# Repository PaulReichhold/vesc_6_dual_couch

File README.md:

# Compact High Power Motor Controller
Based on the VESC-Project of Benjamin Vedder

## Specs
| Spec | Tested to |
|---------|-------|
|__Voltage:__| 6.5V - 50.4V |
|__max Phase Current:__| 180A |
|__max Power (dual, with active cooling)__| 15kW |

> [!NOTE]
> One side has the current measurment inverted (forgot which one it was)

> [!WARNING]
> Use the provided design at your own risk

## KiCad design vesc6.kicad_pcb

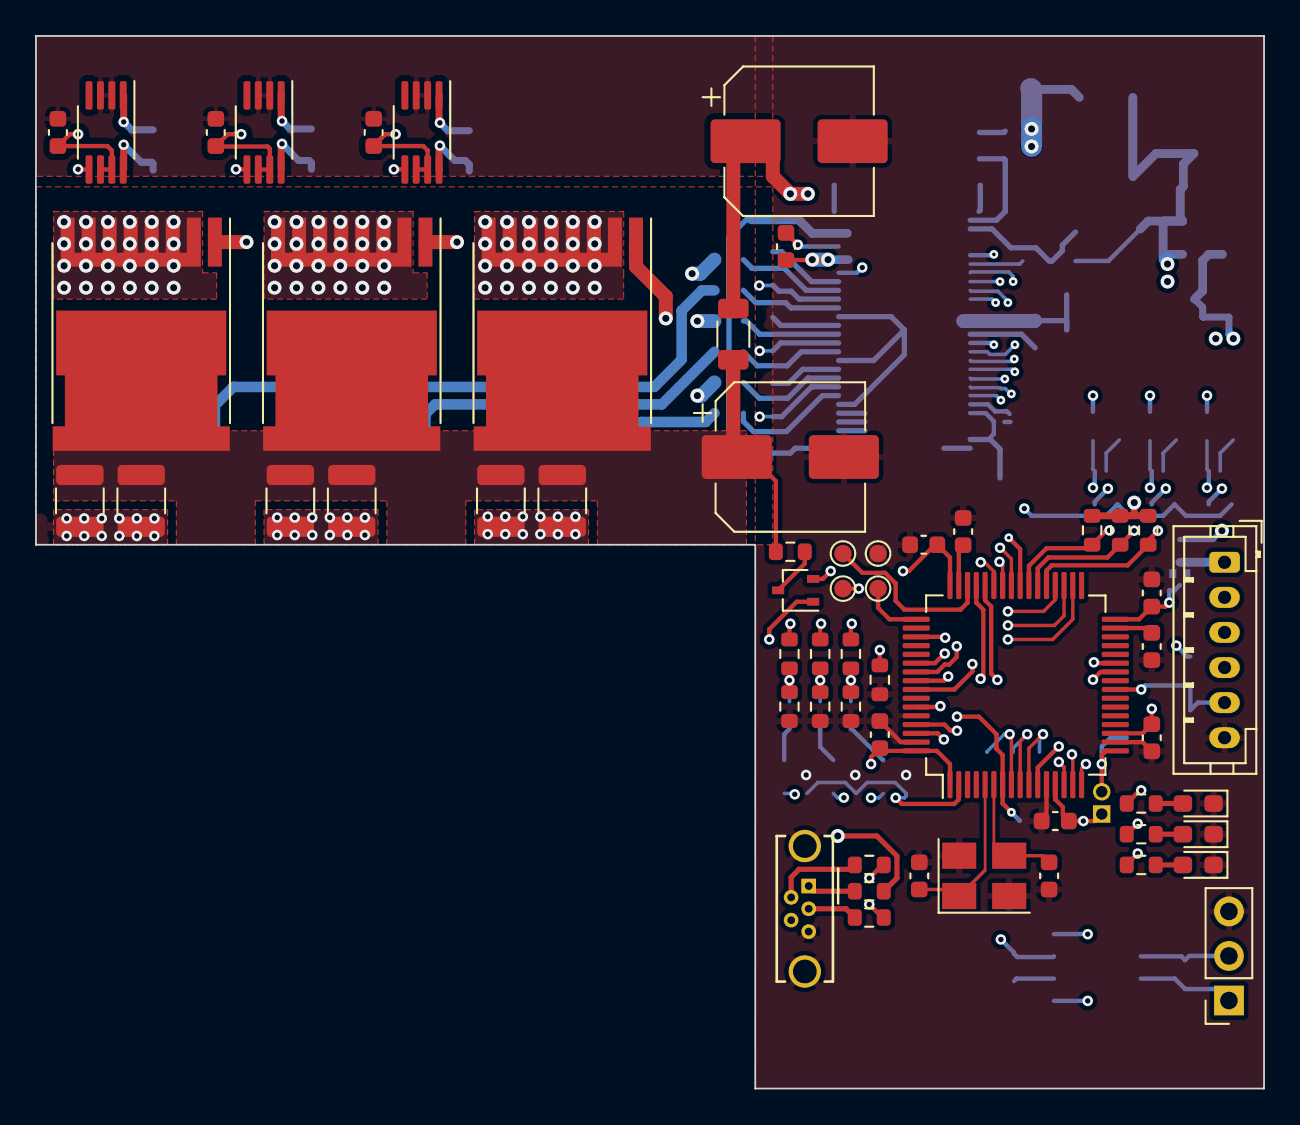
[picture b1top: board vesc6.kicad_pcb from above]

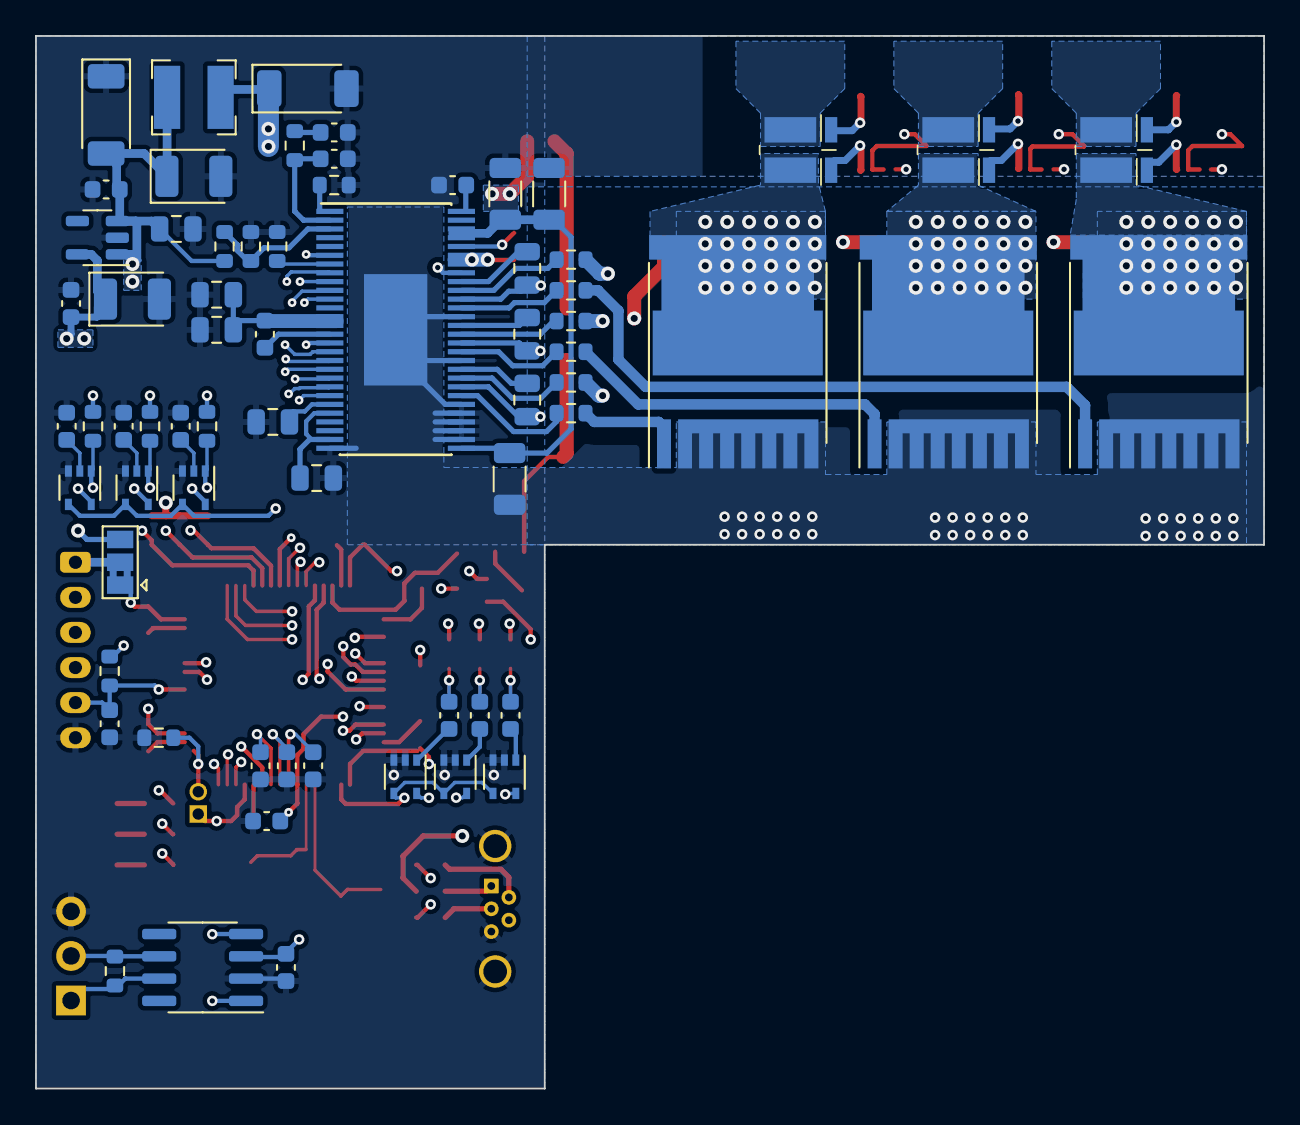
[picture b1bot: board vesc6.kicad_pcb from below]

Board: 4 copper layers, 70.0 x 60.0 mm, 126 parts (67 on the bottom side), 98 nets.

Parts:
C3, C5, C6, C7, C8, C9, C12, C20, C23, C26, C27, C57: 100n; C_0603_1608Metric
C10, C11: 15p; C_0603_1608Metric
C13, C14: 1u; C_0603_1608Metric
C15: 6n8; C_0603_1608Metric
C16, C17, C18, C21, C33: 2.2u; C_0805_2012Metric
C19: 120p; C_0603_1608Metric
C22: 22n; C_0603_1608Metric
C24, C39, C46, C52: 15n; C_0603_1608Metric
C25, C31, C32: 4.7u; C_1206_3216Metric
C28, C29, C30: 220n; C_0805_2012Metric
C34, C37: 100u; CP_EIA-3528-21_Kemet-B
C35, C36, C38, C44, C51: 2.2u; C_0603_1608Metric
C40, C48, C53: 1n; C_0603_1608Metric
C41, C42, C49, C50, C54, C55: 4.7u; C_1210_3225Metric
C56, C58: 22u; CP_Elec_8x6.2
D5: GRN; LED_0603_1608Metric_Pad1.05x0.95mm_HandSolder
D6: RED; LED_0603_1608Metric_Pad1.05x0.95mm_HandSolder
D7: BLU; LED_0603_1608Metric_Pad1.05x0.95mm_HandSolder
D8: D_Schottky; D_SOD-128
D9: 5V; D_SOD-128
FB1: FerriteBead; R_1206_3216Metric
J1: Main; PinSocket_1x03_P2.54mm_Vertical
J2: HALL_ENC; JST_PH_B6B-PH-K_1x06_P2.00mm_Vertical
J6: USB; USB_Micro-B_Wuerth_614105150721_Vertical_CircularHoles
L1: 22u; L_Bourns-SRN4018
Q1: DMN62D0UW; SOT-323_SC-70
Q2, Q3, Q4, Q5, Q6, Q7: HYG015N10NS1TA; Infineon_PG-HSOF-8-1
R6, R7, R8, R21, R25, R27, R29: 2.2k; R_0603_1608Metric
R10: 0; R_0603_1608Metric
R11, R23, R30: 10k; R_0603_1608Metric
R12, R13: 22; R_0603_1608Metric
R14, R15: 220; R_0603_1608Metric
R16, R34, R38, R40: 1k; R_0603_1608Metric
R17: 3.3k; R_0603_1608Metric
R18: 18k; R_0603_1608Metric
R19: 15k; R_0603_1608Metric
R20, R24, R26: 39k; R_0603_1608Metric
R22: 220k; R_0603_1608Metric
R28: 39K; R_0603_1608Metric
R31, R35, R39: 0.5m; BVN_1216
R32, R33, R36, R37, R41, R42: 4.7; R_0603_1608Metric
R43: 120; R_0603_1608Metric
SW1: SENS_VOLTAGE; SolderJumper-3_P1.3mm_Bridged2Bar12_Pad1.0x1.5mm
TH1: NTC; PinHeader_1x02_P1.27mm_Vertical
TP1: SWCLK; TestPoint_Pad_D1.0mm
TP2: SWDIO; TestPoint_Pad_D1.0mm
TP3: NRST; TestPoint_Pad_D1.0mm
TP4: GND; TestPoint_Pad_D1.0mm
U1: STM32F405RGTx; LQFP-64_10x10mm_P0.5mm
U2, U4, U5, U8, U9, U11: Mc74VHC1GT66; SOT-353_SC-70-5
U3: DRV8301DCAR; HTSSOP-56-1EP_6.1x14mm_P0.5mm_EP3.61x6.35mm
U6: TLV73333PDBV; SOT-23-5
U7, U10, U12: AD8418; MSOP-8_3x3mm_P0.65mm
U14: SN65HVD232; SOIC-8_3.9x4.9mm_P1.27mm
Y1: 8M; Crystal_SMD_EuroQuartz_MT-4Pin_3.2x2.5mm_HandSoldering

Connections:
/VESC_Right/3.3V: C5.1, C6.1, C7.1, C8.1, C9.1, C36.1, C37.1, C38.2, C44.2, C51.2, C57.1, R11.2, R16.2, SW1.1 (A), TH1.1, U1.1 (VBAT), U1.13 (VDDA), U1.19 (VDD), U1.32 (VDD), U1.48 (VDD), U1.64 (VDD), U2.5 (VCC), U3.49 (VDD_SPI), U4.5 (VCC), U5.5 (VCC), U6.5 (OUT), U7.6 (VS), U7.7 (REF1), U8.5 (VCC), U9.5 (VCC), U10.6 (VS), U10.7 (REF1), U11.5 (VCC), U12.6 (VS), U12.7 (REF1), U14.3 (VCC)
/VESC_Right/5V: C33.1, C34.1, C35.1, D9.2 (A2), L1.2, Q1.1 (G), R10.2, R18.2, SW1.3 (C), U6.1 (IN), U6.3 (EN)
/VESC_Right/CAN/RX: U1.61 (PB8), U14.4 (R)
/VESC_Right/CAN/TX: U1.62 (PB9), U14.1 (D)
/VESC_Right/CAN_H: J1.1, R43.1, U14.7 (CANH)
/VESC_Right/CAN_L: J1.2, R43.2, U14.6 (CANL)
/VESC_Right/DRV8301/CS: U1.40 (PC9), U3.8 (*SCS)
/VESC_Right/DRV8301/EN_GATE: U1.57 (PB5), U3.16 (EN_GATE)
/VESC_Right/DRV8301/FAULT: U1.59 (PB7), U3.6 (*FAULT)
/VESC_Right/DRV8301/GH_A: R32.1, U3.47 (GH_A)
/VESC_Right/DRV8301/GH_B: R36.1, U3.42 (GH_B)
/VESC_Right/DRV8301/GH_C: R41.1, U3.37 (GH_C)
/VESC_Right/DRV8301/GL_A: R33.1, U3.45 (GL_A)
/VESC_Right/DRV8301/GL_B: R37.1, U3.40 (GL_B)
/VESC_Right/DRV8301/GL_C: R42.1, U3.35 (GL_C)
/VESC_Right/DRV8301/INH_A: U1.41 (PA8), U3.17 (INH_A)
/VESC_Right/DRV8301/INH_B: U1.42 (PA9), U3.19 (INH_B)
/VESC_Right/DRV8301/INH_C: U1.43 (PA10), U3.21 (INH_C)
/VESC_Right/DRV8301/INL_A: U1.34 (PB13), U3.18 (INL_A)
/VESC_Right/DRV8301/INL_B: U1.35 (PB14), U3.20 (INL_B)
/VESC_Right/DRV8301/INL_C: U1.36 (PB15), U3.22 (INL_C)
/VESC_Right/DRV8301/SCLK: U1.51 (PC10), U3.11 (SCLK)
/VESC_Right/DRV8301/SDI: U1.56 (PB4), U3.9 (SDI)
/VESC_Right/DRV8301/SDO: U1.55 (PB3), U3.10 (SDO)
/VESC_Right/DRV8301/SENS_A: C20.1, R20.2, R21.2, U1.14 (PA0)
/VESC_Right/DRV8301/SENS_B: C23.1, R24.2, R25.2, U1.15 (PA1)
/VESC_Right/DRV8301/SENS_C: C26.1, R26.2, R27.2, U1.16 (PA2)
/VESC_Right/DRV8301/SENS_FILTERED: U1.2 (PC13), U2.4 (ON_OFF), U4.4 (ON_OFF), U5.4 (ON_OFF)
/VESC_Right/DRV8301/SENS_SUPPLY: Q1.2 (S), R29.1, U1.11 (PC3)
/VESC_Right/DRV8301/SH_B: C29.1, Q4.2 (S), Q5.3 (D), R24.1, R35.1, U3.41 (SH_B)
/VESC_Right/DRV8301/SH_C: C30.1, Q4.1 (G), Q6.2 (S), Q7.3 (D), R26.1, R36.2, R39.1, U3.36 (SH_C)
/VESC_Right/DRV8301/SUPPLY: C41.1, C42.1, C49.1, C50.1, C54.1, C55.1, C56.1, FB1.2, Q2.3 (D), Q4.3 (D), Q6.3 (D), R28.1
/VESC_Right/DRV8301/Supply_Filterted: C25.1, C31.1, C32.1, C58.1, FB1.1, U3.29 (PVDD1), U3.53 (PVDD2), U3.54 (PVDD2)
/VESC_Right/MCU/ADC_TEMP: R30.2, TH1.2, U1.17 (PA3)
/VESC_Right/MCU/CURRENT_1: C40.2, R34.1, U1.8 (PC0), U8.1 (IO_XA)
/VESC_Right/MCU/CURRENT_2: C48.2, R38.1, U1.9 (PC1), U9.1 (IO_XA)
/VESC_Right/MCU/CURRENT_3: C53.2, R40.1, U1.10 (PC2), U11.1 (IO_XA)
/VESC_Right/MCU/CURR_FILTER_ON: U1.54 (PD2), U8.4 (ON_OFF), U9.4 (ON_OFF), U11.4 (ON_OFF)
/VESC_Right/MCU/HALL_1: J2.2, R6.2, U1.37 (PC6)
/VESC_Right/MCU/HALL_2: J2.3, R7.2, U1.38 (PC7)
/VESC_Right/MCU/HALL_3: J2.4, R8.2, U1.39 (PC8)
/VESC_Right/MCU/LED_GREEN: R14.2, U1.26 (PB0)
/VESC_Right/MCU/LED_RED: R15.2, U1.27 (PB1)
/VESC_Right/MCU/NRST: C12.1, TP3.1, U1.7 (NRST)
/VESC_Right/MCU/SWCLK: TP1.1, U1.49 (PA14)
/VESC_Right/MCU/SWDIO: TP2.1, U1.46 (PA13)
/VESC_Right/MCU/TEMP_MOTOR: C3.1, J2.5, R11.1, U1.24 (PC4)
/VESC_Right/MCU/USB_D_N: R13.2, U1.44 (PA11)
/VESC_Right/MCU/USB_D_P: R12.2, U1.45 (PA12)
/VESC_Right/Power/C_A: R34.2, U7.5 (OUT)
/VESC_Right/Power/C_B: R38.2, U10.5 (OUT)
/VESC_Right/Power/C_C: R40.2, U12.5 (OUT)
/VESC_Right/SH_A: C28.1, Q2.2 (S), Q3.3 (D), R20.1, R31.1, U3.46 (SH_A)
GND: C3.2, C5.2, C6.2, C7.2, C8.2, C9.2, C10.2, C11.2, C12.2, C13.2, C14.2, C15.2, C16.2, C17.2, C18.2, C19.2, C21.2, C24.1, C25.2, C31.2, C32.2, C33.2, C34.2, C35.2, C36.2, C37.2, C38.1, C39.1, C40.1, C41.2, C42.2, C44.1, C46.1, C48.1, C49.2, C50.2, C51.1, C52.1, C53.1, C54.2, C55.2, C56.2, C57.2, C58.2, D5.1 (K), D6.1 (K), D7.1 (K), D8.2 (A), D9.1 (A1), J1.3, J2.6, J6.5 (GND), J6.6 (Shield), Q3.2 (S), Q5.2 (S), Q7.2 (S), R17.1, R21.1, R22.1, R23.2, R25.1, R27.1, R29.2, R30.1, TP4.1, U1.12 (VSSA), U1.18 (VSS), U1.60 (BOOT0), U1.63 (VSS), U2.2 (IO_YA), U2.3 (GND), U3.28 (AGND), U3.30 (SP2), U3.31 (SN2), U3.32 (SP1), U3.33 (SN1), U3.34 (SL_C), U3.39 (SL_B), U3.44 (SL_A), U3.57 (EPAD), U4.2 (IO_YA), U4.3 (GND), U5.2 (IO_YA), U5.3 (GND), U6.2 (GND), U7.2 (GND), U7.3 (REF2), U8.3 (GND), U9.3 (GND), U10.2 (GND), U10.3 (REF2), U11.3 (GND), U12.2 (GND), U12.3 (REF2), U14.2 (GND), Y1.2, Y1.4
unnamed: C15.1, R19.1
unnamed: D5.2 (A), R14.1
unnamed: D6.2 (A), R15.1
unnamed: D7.2 (A), R16.1
unnamed: C27.1, D8.1 (K), L1.1, U3.50 (PH), U3.51 (PH)
unnamed: J2.1, R6.1, R7.1, R8.1, SW1.2 (B)
unnamed: J6.3 (D+), R12.1
unnamed: J6.2 (D-), R13.1
unnamed: J6.1 (VBUS), R10.1
unnamed: Q1.3 (D), R28.2
unnamed: Q2.1 (G), R32.2
unnamed: Q3.1 (G), R33.2
unnamed: Q5.1 (G), R37.2
unnamed: Q6.1 (G), R41.2
unnamed: Q7.1 (G), R42.2
unnamed: C10.1, U1.5 (PH0), Y1.1
unnamed: C11.1, U1.6 (PH1), Y1.3
unnamed: C13.1, U1.31 (VCAP_1)
unnamed: C14.1, U1.47 (VCAP_2)
unnamed: C20.2, U2.1 (IO_XA)
unnamed: C21.1, U3.24 (REF), U3.27 (AVDD)
unnamed: C28.2, U3.48 (BST_A)
unnamed: C29.2, U3.43 (BST_B)
unnamed: C27.2, U3.52 (BST_BK)
unnamed: C30.2, U3.38 (BST_C)
unnamed: C19.1, R19.2, U3.2 (COMP)
unnamed: C16.1, C17.1, C22.1, U3.13 (GVDD), U3.14 (CP1)
unnamed: C22.2, U3.15 (CP2)
unnamed: R23.1, U3.7 (DTC)
unnamed: C18.1, U3.23 (DVDD)
unnamed: R22.2, U3.1 (RT_CLK)
unnamed: C24.2, U3.56 (SS_TR)
unnamed: R17.2, R18.1, U3.3 (VSENSE)
unnamed: C23.2, U4.1 (IO_XA)
unnamed: C26.2, U5.1 (IO_XA)
unnamed: R31.2, U7.8 (IN+)
unnamed: R31.3, U7.1 (IN-)
unnamed: C39.2, U8.2 (IO_YA)
unnamed: C46.2, U9.2 (IO_YA)
unnamed: R35.2, U10.8 (IN+)
unnamed: R35.3, U10.1 (IN-)
unnamed: C52.2, U11.2 (IO_YA)
unnamed: R39.2, U12.8 (IN+)
unnamed: R39.3, U12.1 (IN-)

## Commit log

2024-10-10 Init
